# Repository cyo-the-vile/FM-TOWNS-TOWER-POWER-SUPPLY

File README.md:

# FM-TOWNS-TOWER-POWER-SUPPLY
Replacement Power supply for FMT Tower units

This is a replacement for the aging FM Towns power supply.  It's a very well known fact in the niche FM Towns community that the power supply in the Tower models has chronic failure issues. This power supply revolves around using an ACDC converter with an ITX Pico PSU controlled by an Arduino Pro Micro.

This power supply can be used for the following FM Towns computers:

-MODEL 1
-MODEL 2
-SF
-SH
-1F
-2F
-1H
-2H
-10F
-20F
-40H
-80H
-CX10
-CX20
-CX40
-CX100
-SF2
-SH2

To assemble you need to program an Arduino Pro Micro in the Arduino IDE.  Once the Arduino is programmed solder the pin headers and Arduino to the PCB.

After that simply solder everything else.

The Arduino runs on the 5V Standby of the Pico PSU and controls the power on via original power button and also the TownsOS power off feature.

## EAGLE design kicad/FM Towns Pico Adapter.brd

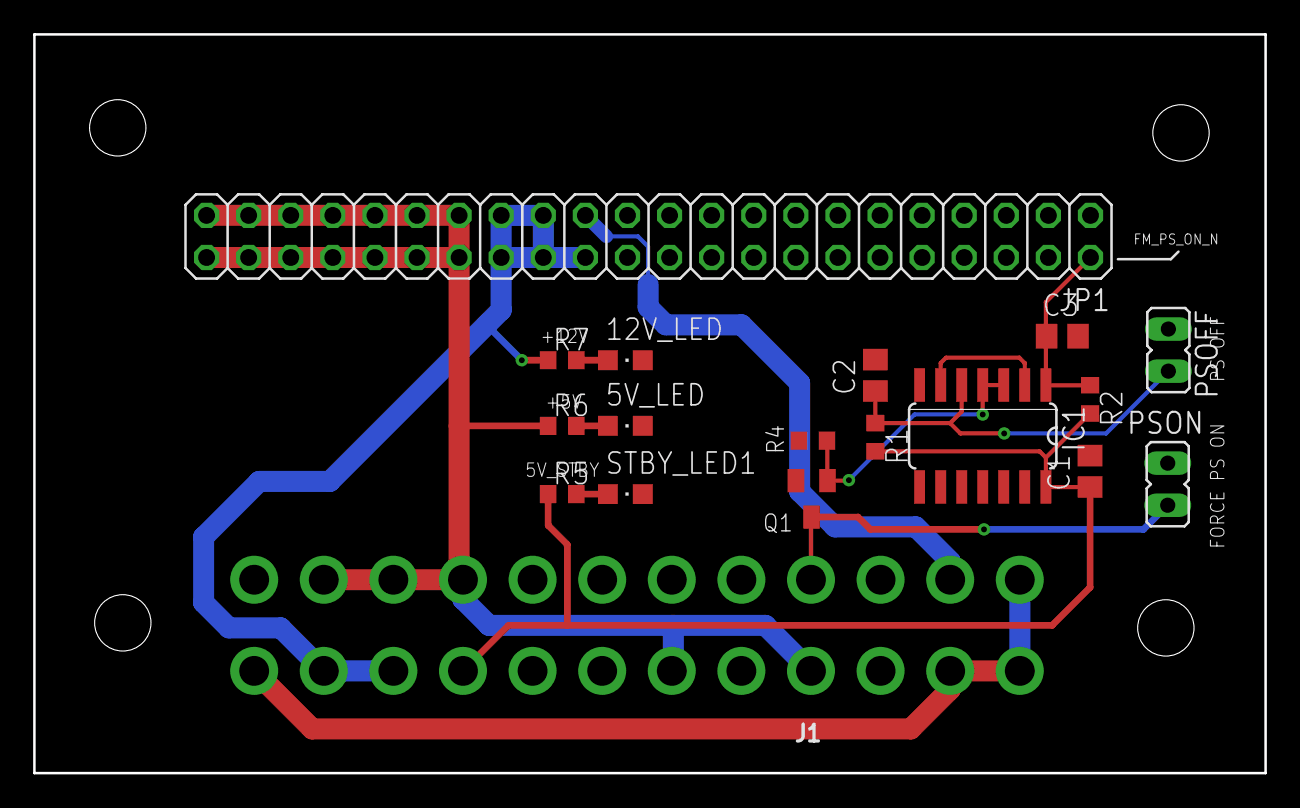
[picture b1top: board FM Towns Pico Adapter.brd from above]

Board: 2 copper layers, 74.3 x 44.6 mm, 18 parts (0 on the bottom side), 14 nets.

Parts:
5V_LED, 12V_LED: CHIPLED_0805
C1, C2, C3: 100nF; C0805
IC1: 74HC00D; SO14
J1: ATX24RH; ATX24_RIGHT_ANGLE
JP1: 2X22
PSOFF: JP1
PSON: JP1
Q1: BC847; SOT23
R1, R2, R4: 1K; R0603
R5, R6: 220R; R0603
R7: 680R; R0603
STBY_LED1: CHIPLED_0805

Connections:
5V_STBY: C1.1, IC1.14, J1.9, R1.2, R2.2, R5.1
+3V3: J1.1, J1.2, J1.12, J1.13
+5V: J1.4, J1.6, J1.21, J1.22, J1.23, JP1.31, JP1.32, JP1.33, JP1.34, JP1.35, JP1.36, JP1.37, JP1.38, JP1.39, JP1.40, JP1.41, JP1.42, JP1.43, JP1.44, R6.1
+12V: J1.10, J1.11, JP1.26, JP1.27, JP1.28, JP1.29, JP1.30, R7.1
-12V: J1.14, JP1.25
ATX_PS_ON_N: J1.16, PSON.1, Q1.3
FM_PS_OFF_N: C2.1, IC1.5, PSOFF.2, R1.1
FM_PS_ON_N: C3.1, IC1.1, JP1.2, R2.1
GND: 5V_LED.C, 12V_LED.C, C1.2, C2.2, C3.2, IC1.7, IC1.9, IC1.10, IC1.12, IC1.13, J1.3, J1.5, J1.7, J1.15, J1.17, J1.18, J1.19, J1.24, JP1.3, JP1.4, JP1.5, JP1.6, JP1.7, JP1.8, JP1.9, JP1.10, JP1.11, JP1.12, JP1.13, JP1.14, JP1.15, JP1.16, JP1.17, JP1.18, JP1.19, JP1.20, JP1.21, JP1.22, JP1.23, JP1.24, PSOFF.1, PSON.2, Q1.2, R4.1, STBY_LED1.C
unnamed: IC1.2, IC1.6
unnamed: R5.2, STBY_LED1.A
unnamed: 5V_LED.A, R6.2
unnamed: 12V_LED.A, R7.2
PS_ON_TTL: IC1.3, IC1.4, Q1.1, R4.2

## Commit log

2021-04-14 GERBERS
    Factory output files for PCB fabrication
2021-04-14 Kicad Files
    Kicad files for editing PCB
2021-04-14 Arduino Script
    Script to configure Arduino Nano
2021-04-14 BOM file
    Bill of materials
2021-04-14 Update BOM

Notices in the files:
parts and their libraries:
SparkFun-Connectors: Licensing: Creative Commons ShareAlike 4.0 International - https://creativecommons.org/licenses/by-sa/4.0
